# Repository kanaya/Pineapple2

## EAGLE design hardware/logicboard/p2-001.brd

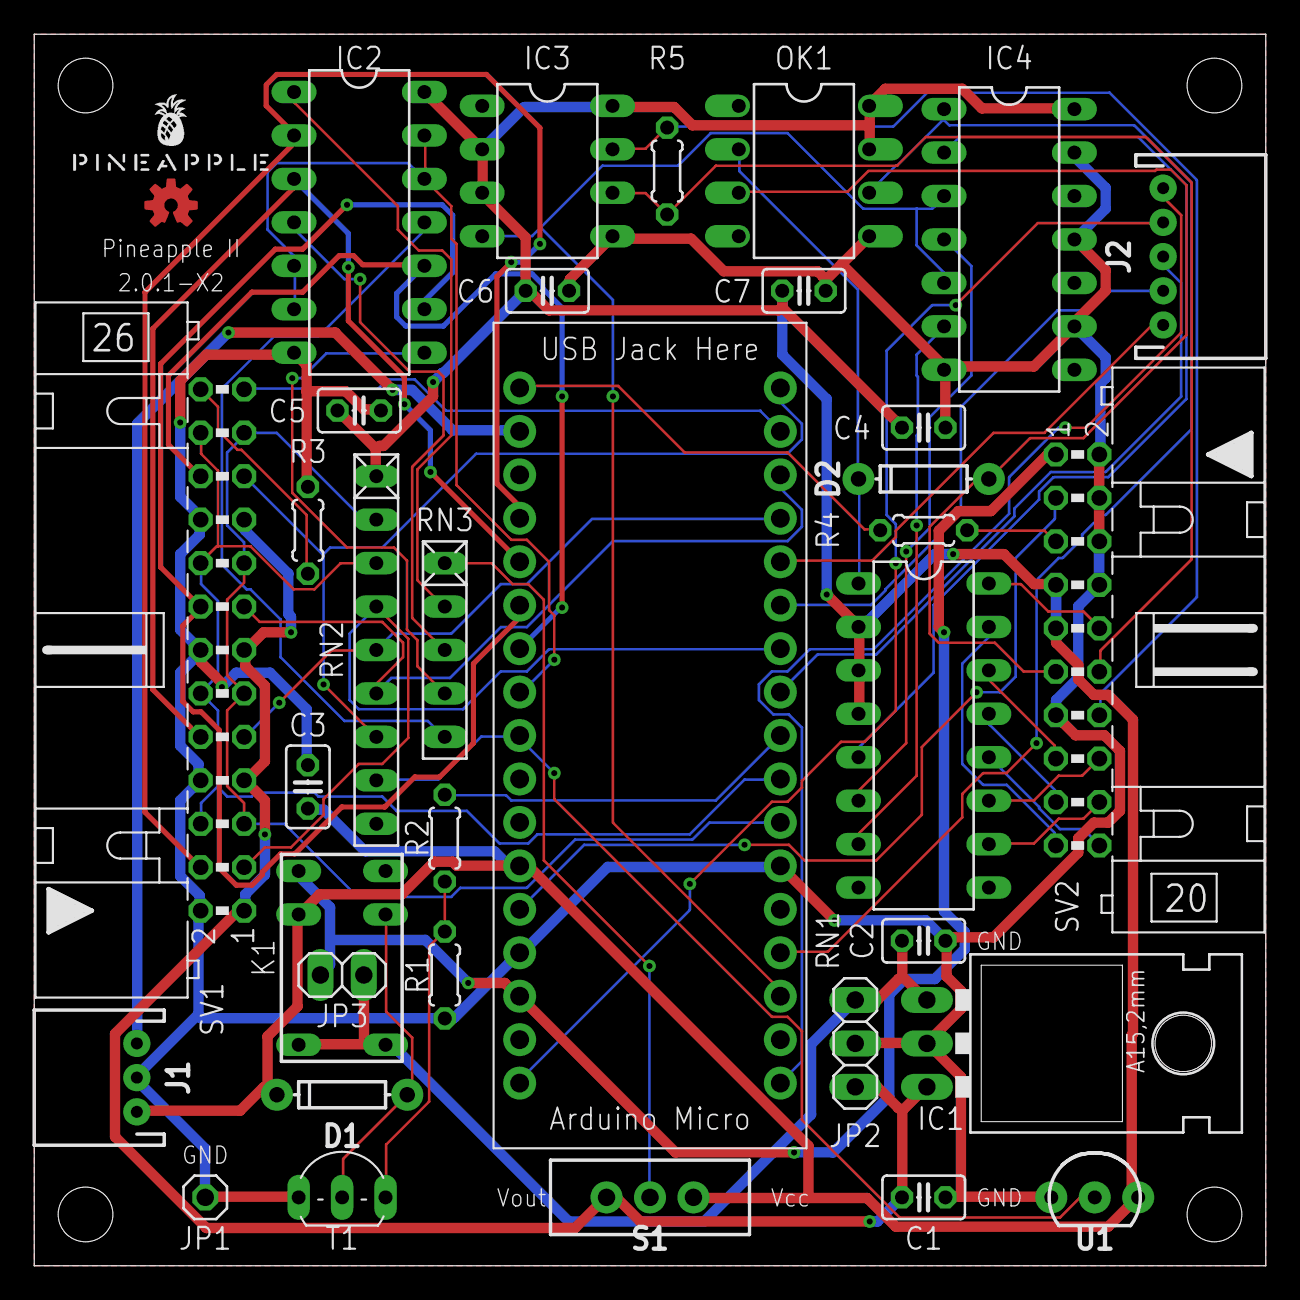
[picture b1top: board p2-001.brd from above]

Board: 2 copper layers, 72.0 x 72.0 mm, 36 parts (0 on the bottom side), 52 nets.

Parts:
C1, C3, C4, C5, C6, C7: 103; C025-025X050
C2: 104; C025-025X050
D1, D2: DIODE-1N4148
IC1: 5V; 78XXL
IC2: 4066N; DIL14
IC3: LTC485N; DIL08
IC4: 74LS07N; DIL14
J1: Power; JST-3-PTH
J2: Display; JST-5-PTH
JP1: GNDPIN; 1X01
JP2: PWRSPL; 1X03
JP3: RELAYJUMP; 1X02
K1: G5V1
LOGO1: OSHW-LOGOS-COPPER; OSHW-LOGO-S_COPPER
MC1: ARDUINOMICRO
OK1: 6N137; DIL08
R1: 47k; 0204/5
R2: 1k; 0204/5
R3, R4: 160; 0204/5
R5: 120; 0204/5
RN1: 220; DIL16
RN2: 4.7k; RN-9
RN3: 10k; RN-5
S1: AnalogPullUpSelect; SWITCH_SPDT_PTH_11.6X4.0MM
SV1: ML26L
SV2: ML20L
T1: 2SC1815; TO92-ECB
U1: DS18B20; TO-92-AMMO
U$1: PINEAPPLE450_SILK

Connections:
+5V: C1.1, IC1.OUT, JP2.3, S1.1, SV1.1, SV1.7, SV1.13, SV1.19
+12V: JP3.1, K1.1, MC1.P$20, SV2.1
A1: IC2.2, MC1.P$31, SV1.4
A2: IC2.3, MC1.P$30, SV1.10
A3: IC2.9, MC1.P$29, SV1.16
A4: IC2.10, MC1.P$28, SV1.22
D1: MC1.P$7, RN2.4, SV1.3
D2: MC1.P$4, RN2.5, SV1.9
D3: MC1.P$3, RN2.6, SV1.15
D4: MC1.P$1, RN2.7, SV1.21
FLED: MC1.P$2, SV1.25
GND: C1.2, C2.2, C3.2, C4.2, C5.2, C6.2, C7.2, IC1.GND, IC2.7, IC3.5, IC4.7, IC4.9, IC4.11, IC4.13, J1.2, JP1.1, JP2.2, MC1.P$12, MC1.P$21, OK1.5, R1.1, R3.2, SV1.2, SV1.8, SV1.14, SV1.20, SV2.2, SV2.4, SV2.6, SV2.8, SV2.13, T1.E, U1.1
GPIO1: J2.3, MC1.P$8
GPIO2: J2.4, MC1.P$6
GPIO3: J2.5, MC1.P$5
LED: MC1.P$34, R4.1
LEDA: R4.2, SV2.5
MIDIINSND: D2.C, OK1.2, RN1.1
MINRTN: D2.A, OK1.3, SV2.11
MINSND: RN1.16, SV2.10
MO1: IC4.4, RN1.6
MO1RTN: RN1.11, SV2.16
MO1SND: RN1.14, SV2.15
MO2: IC4.6, RN1.7
MO2RTN: RN1.10, SV2.18
MO2SND: RN1.13, SV2.17
MOSI: J2.1, MC1.P$17
MTH: IC4.2, RN1.5
MTHRTN: RN1.12, SV2.20
MTHSND: RN1.15, SV2.19
MTX+: IC3.6, R5.1, SV2.12
MTX-: IC3.7, R5.2, SV2.14
unnamed: IC2.1, RN3.2
unnamed: R3.1, SV1.26
unnamed: IC2.4, RN3.3
unnamed: IC2.8, RN3.4
unnamed: IC2.11, RN3.5
PULLUP: IC2.5, IC2.6, IC2.12, IC2.13, MC1.P$27
RLY: MC1.P$9, R2.2
RLYDRV: R1.2, R2.1, T1.B
RLYSNK: D1.A, K1.9, T1.C
RST: MC1.P$13, SV2.3
RX: IC4.1, MC1.P$14, OK1.6
SCL: MC1.P$10, RN2.3, SV1.6, SV1.12, SV1.18, SV1.24
SCLK: J2.2, MC1.P$18
SDA: MC1.P$11, RN2.2, SV1.5, SV1.11, SV1.17, SV1.23
THS: MC1.P$26, RN2.8, U1.2
TX: IC3.4, IC4.3, IC4.5, MC1.P$15
VCC: C3.1, C4.1, C5.1, C6.1, C7.1, D1.C, IC2.14, IC3.2, IC3.3, IC3.8, IC4.14, J1.1, K1.2, MC1.P$23, OK1.7, OK1.8, RN1.2, RN1.3, RN1.4, RN2.1, S1.3, SV2.7, SV2.9, U1.3
VDD: J1.3, MC1.P$33
VIN: C2.1, IC1.IN, JP2.1, JP3.2, K1.5, K1.6
VPULLUP: RN3.1, S1.2

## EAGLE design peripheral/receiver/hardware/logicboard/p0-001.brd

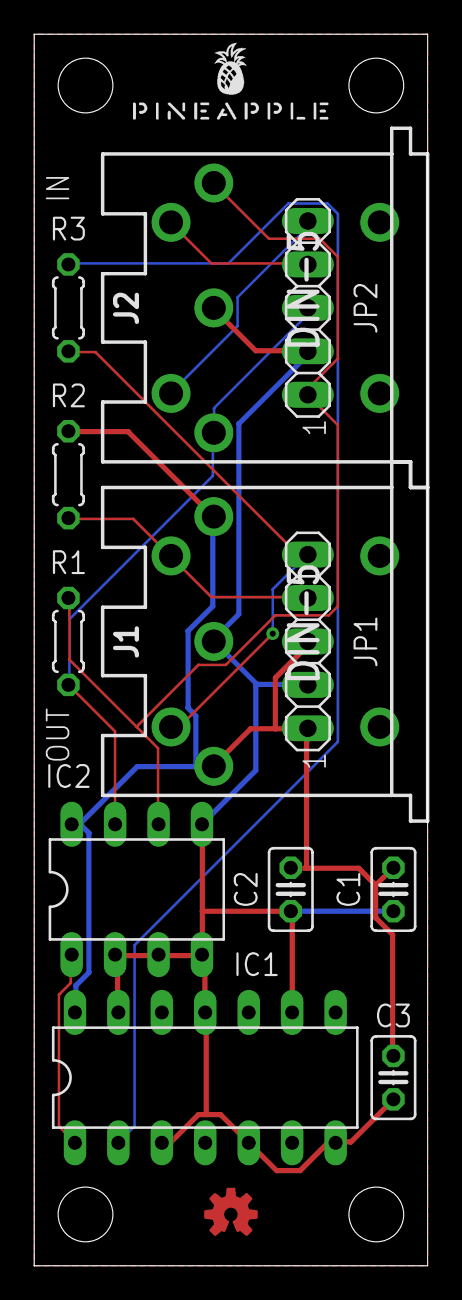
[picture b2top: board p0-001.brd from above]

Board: 2 copper layers, 23.0 x 72.0 mm, 14 parts (0 on the bottom side), 10 nets.

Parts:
C1: 104; C025-025X050
C2, C3: 103; C025-025X050
IC1: 74LS07N; DIL14
IC2: LTC485N; DIL08
J1, J2: DIN5; DIN5-RA-PTH
JP1, JP2: 1X05
LOGO1: OSHW-LOGOS-COPPER; OSHW-LOGO-S_COPPER
R1: 120; 0204/5
R2, R3: 220; 0204/5
U$1: PINEAPPLE450

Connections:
DUMMY4: J2.4, JP2.4
DUMMY5: J2.5, JP2.5
GND: C1.2, C2.2, C3.2, IC1.3, IC1.5, IC1.7, IC1.9, IC1.11, IC1.13, IC2.2, IC2.3, IC2.4, IC2.5, J1.2, J2.2, JP1.2, JP2.2
MOUTRTN: J1.5, JP1.5, R3.1
MOUTSND: J1.4, JP1.4, R2.1
unnamed: IC1.2, R3.2
RX+: IC2.6, J2.1, JP2.1, R1.2
RX-: IC2.7, J2.3, JP2.3, R1.1
TX: IC1.1, IC2.1
VCC: C1.1, C2.1, C3.1, IC1.14, IC2.8, J1.1, J1.3, JP1.1, JP1.3, R2.2

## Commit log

2020-01-05 Initinal commit.
2020-01-05 Titles of panels.
2020-01-05 Note on thermal sensor and breaker.
2020-01-06 Added missing frame of Panel 4.
2020-01-06 Almost brank schematic.
2020-01-06 Schematic.
2020-01-06 Refine of schematic and board.
2020-01-07 Added gitignore.
2020-01-07 Layout.
2020-01-07 Board design.
2020-01-07 Nothing.
2020-01-07 Silk
2020-01-08 XLED terminals.
2020-01-08 Silk.
2020-01-08 Fixed internal connector layouts.
2020-01-08 Fixed typo.
2020-01-09 Fixed error.
2020-01-09 Clean up.
2020-01-09 Added restricted area.
2020-01-09 Clean up of schematic.
2020-01-09 Version 2.0.0 -> 2.0.1
2020-01-09 Nothing was changed except for silk.
2020-01-09 Added PDF of schematic.
2020-01-09 Modified schematic and board for the better readability.
2020-01-09 Updated PDF.
2020-01-09 Real hotfix! Now pull-ups to Analog In are connected to Vout, not Vcc.
2020-01-10 Added pull-up selector.
2020-01-10 Jumper -> SW.
2020-01-11 Changed netclass of VPULLUP to power.
2020-01-11 Replaced back-panel SW to LEDSW. Now Back port is incompatible to 2.0.0-X.
2020-01-11 Changed diamiter of thecenter-upper hole of the back-panel to 8.2mm so that it can hold LEDSW.
2020-01-11 Comment on future MPU change.
2020-01-12 Note on experimental pinout for Pro Mini.
2020-01-12 Note on experimental pinout for Pro Micro.
2020-01-12 Added RS-422 TX driver.
2020-01-12 Fixed unconnected wires.
2020-01-12 Imported schematic of Pineapple Zero.
2020-01-12 Added DX receiver.
2020-01-12 Now pin 3 of MIDI In is connected to Vcc.
2020-01-12 Alternative Qi connectors.
2020-01-12 Fixed description of MIDI connectors.
2020-01-13 Minor fix of silk.
2020-01-14 Very minor bugfix to adopt to Markdown standard.
2020-01-25 Fixed connection of TLP552 to the power pins.
2020-01-25 Moved Arduino Micro downward so that it can safely hold USB connector.
2020-01-25 Changed fonts for better looking.
2020-01-25 "PINEAPPLE.CC" on the back surface.
2020-01-25 Check-list 1.
2020-01-25 Checked several pins.
2020-01-27 Moved Arduino Micro downward.
2020-01-27 Optimized PCB layout.
2020-01-27 Back LED is now connected to D13 (again).
2020-01-27 Single front LED.
2020-01-28 Front panel now has only 1 LED hole.
2020-01-28 Pinout.
2020-01-28 More change.
2020-01-28 Renumbered parts.
2020-01-29 Readability.
2020-01-29 Pinout for MKR version.
2020-01-29 Changed signaling.
2020-01-29 Arduino Nano Every pinout.

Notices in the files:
parts and their libraries:
SparkFun-DiscreteSemi: Licensing: Creative Commons ShareAlike 4.0 International - https://creativecommons.org/licenses/by-sa/4.0
